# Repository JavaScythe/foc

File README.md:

# foc
Hyper realistic two-channel sim racing seatbelt tensioner with two 48V 54+54A FOC motors and controller that blows commercial 1300$ solutions out of the water

Specifically, it is high torque low latency that comes with its own software with support for real dynamic frequency effects for haptic feedback

### PLEASE see [JOURNAL.md](JOURNAL.md)

### Why?
- HackClub's great initiative [highway](https://highway.hackclub.com): not just "free money" but a nice community of beginners and advanced that help each other
- Lack of respect for realism in sim racing: All too often "immersion" devices are just smoke and mirrors to generate profit, lacking careful design for realism, and the community defends this.
- Vastly overpriced consumer solutions: Really? 1300$ for something that can be surpassed by a consumer with 350$?
- Fun but complex to build toy: Using the rig is fun, but building stuff for it is better

### Pictures

### BOM
|Name          |Quantity|Price Total  |Link  |
|--------|-------|--------|------|
|ODrive3.6 56V|1|60$    |alibaba.com/product-detail/ODrive3-6-FOC-BLDC-Servo-Dual_1601406724288.html|
|S70BL146-430|2|120$|alibaba.com/product-detail/S70BL146-430-Brushless-Dc-Motor-High_1600943342358.html|
|4 Point Belt|1|19$|aliexpress.us/item/3256807037196658.html|
|2kw 40A 48V PSU|1|100$|alibaba.com/product-detail/High-Quality-2000W-48V-41-6A_1600901714728.html|
|SimHub License+Motion License|1|45€|simhubdash.com/simhub-motion-addon-licence/|

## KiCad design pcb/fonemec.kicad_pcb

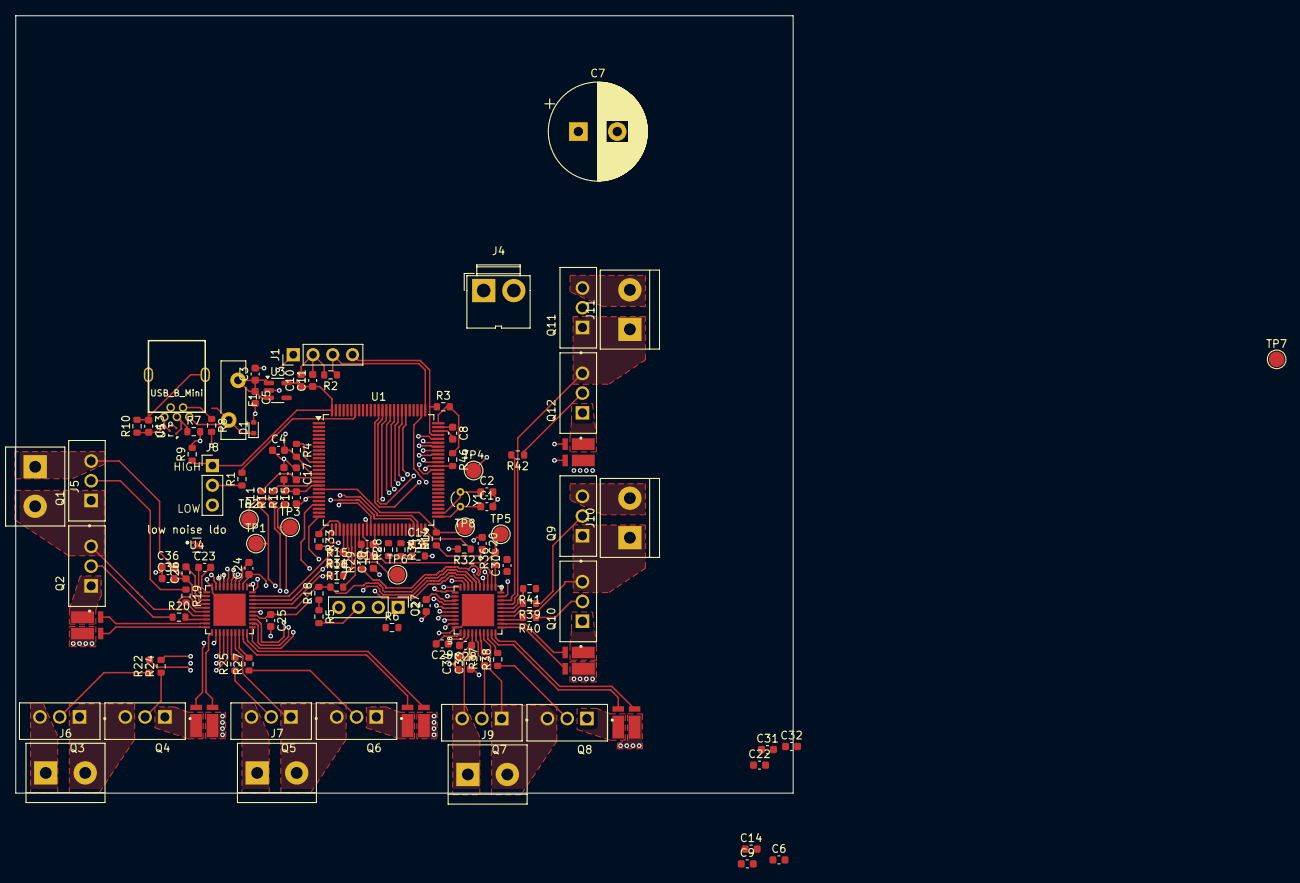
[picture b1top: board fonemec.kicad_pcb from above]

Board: 4 copper layers, 100.0 x 100.0 mm, 120 parts (0 on the bottom side), 122 nets.

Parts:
C1, C2: 22pF; C_0603_1608Metric
C3, C5, C8, C12: 10 µF X7R; C_0603_1608Metric
C4: 0.1uF; C_0603_1608Metric
C6, C10: 10 0nF; C_0603_1608Metric
C7: Low-ESR polymer electrolytic 470uF 63V; CP_Radial_D12.5mm_P5.00mm
C9, C11: 1 µF; C_0603_1608Metric
C13: 1 nF; C_0603_1608Metric
C14, C22, C33, C36: 22uf Ceramic MLCC X7R; C_0603_1608Metric
C15, C16, C17, C18, C19, C20: 1nF; C_0603_1608Metric
C23, C29: X7R 47nF >48V; C_0603_1608Metric
C24, C27: X7R 1uF 6.3V; C_0603_1608Metric
C25, C30: X7R 0.1uF 6.3V; C_0603_1608Metric
C26, C28: X7R 1uF 16V; C_0603_1608Metric
C31: X7R 22uF >63V; C_0603_1608Metric
C32: X7R 0.1uF >63V; C_0603_1608Metric
C34, C35: 0.1uf Ceramic MLCC X7R; C_0603_1608Metric
D1: PESD5V0S1BA; D_SOD-523
F1: ASMD050-2; Fuse_Bourns_MF-RG400
J1: 01x04 SWD; PinHeader_1x04_P2.54mm_Vertical
J2: 01x04 USART; PinHeader_1x04_P2.54mm_Vertical
J3: USB_B_Mini; USB-Mini-B_2leg
J4: 01x02 48V; JWT_A3963_1x02_P3.96mm_Vertical
J5: Motor 1 Phase A; TerminalBlock_bornier-2_P5.08mm
J6: Motor 1 Phase B; TerminalBlock_bornier-2_P5.08mm
J7: Motor 1 Phase C; TerminalBlock_bornier-2_P5.08mm
J8: Conn_01x03_Pin; PinHeader_1x03_P2.54mm_Vertical
J9: Motor 2 Phase A; TerminalBlock_bornier-2_P5.08mm
J10: Motor 2 Phase B; TerminalBlock_bornier-2_P5.08mm
J11: Motor 2 Phase C; TerminalBlock_bornier-2_P5.08mm
Q1, Q2, Q3, Q4, Q5, Q6, Q7, Q8, Q9, Q10, Q11, Q12: CSD19536KCS; TO254P1036X470X1965-3
R1, R2, R3, R4, R5: 100K; R_0603_1608Metric
R6: 1K; R_0603_1608Metric
R7, R8, R15, R16, R17, R28, R31, R35: 22; R_0603_1608Metric
R9: 1.5K; R_0603_1608Metric
R10: 1M; R_0603_1608Metric
R11, R12, R13, R14, R29, R36: 100; R_0603_1608Metric
R18, R32, R33, R34, R46: 10K; R_0603_1608Metric
R19, R20, R22, R24, R25, R27, R37, R38, R39, R40, R41, R42: 2; R_0603_1608Metric
R21, R23, R26, R43, R44, R45: R_Shunt; RES_WSK12161L000FEA
TP1: TP1SOA; TestPoint_Pad_D2.0mm
TP2: TP1SOB; TestPoint_Pad_D2.0mm
TP3: TP1SOC; TestPoint_Pad_D2.0mm
TP4, TP7: TPGND; TestPoint_Pad_D2.0mm
TP5: TP2SOC; TestPoint_Pad_D2.0mm
TP6: TP2SOB; TestPoint_Pad_D2.0mm
TP8: TP2SOA; TestPoint_Pad_D2.0mm
U1: STM32F405VGTx; LQFP-100_14x14mm_P0.5mm
U3: AP2112K-3.3; SOT-23-5
U4: PTPS7A0218PDQNR; DQN0004A-MFG
U5: TPD2EUSB30; Texas_DRT-3
U7, U8: DRV8323SRTAT; QFN50P600X600X80-41N415X415
Y1: 8Mhz; Crystal_DS26_D2.0mm_L6.0mm_Vertical

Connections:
1CAL: U1.65 (PC8), U7.31 (CAL)
1ENABLE: U1.63 (PC6), U7.30 (ENABLE)
1GHA: R19.2, U7.6 (GHA)
1GHB: R22.2, U7.15 (GHB)
1GHC: R25.2, U7.16 (GHC)
1GLA: R20.2, U7.8 (GLA)
1GLB: R24.2, U7.13 (GLB)
1GLC: R27.2, U7.18 (GLC)
1INHA: U1.67 (PA8), U7.34 (INHA)
1INHB: U1.69 (PA10), U7.36 (INHB)
1INHC: U1.48 (PB11), U7.38 (INHC)
1INLA: U1.68 (PA9), U7.35 (INLA)
1INLB: U1.36 (PB1), U7.37 (INLB)
1INLC: U1.47 (PB10), U7.39 (INLC)
1NFAULT: R46.2, U1.64 (PC7), U7.25 (NFAULT)
1SAN: R21.2, U7.10 (SNA)
1SAP: R21.3, U7.9 (SPA)
1SBN: R23.2, U7.11 (SNB)
1SBP: R23.3, U7.12 (SPB)
1SCN: R26.2, U7.20 (SNC)
1SCP: R26.3, U7.19 (SPC)
1SHA: J5.2, Q1.1 (S), Q2.5 (D), U7.5 (VDRAIN), U7.7 (SHA)
1SHB: J6.2, Q3.1 (S), Q4.5 (D), U7.14 (SHB)
1SHC: J7.2, Q5.1 (S), Q6.5 (D), U7.17 (SHC)
1SOA: C17.2, R11.2, U1.15 (PC0)
1SOB: C16.2, R12.2, U1.16 (PC1)
1SOC: C15.2, R13.2, U1.17 (PC2)
2CAL: U1.88 (PD7), U8.31 (CAL)
2ENABLE: U1.87 (PD6), U8.30 (ENABLE)
2GHA: R37.2, U8.6 (GHA)
2GHB: R39.2, U8.15 (GHB)
2GHC: R41.2, U8.16 (GHC)
2GLA: R38.2, U8.8 (GLA)
2GLB: R40.2, U8.13 (GLB)
2GLC: R42.2, U8.18 (GLC)
2INHA: U1.81 (PD0), U8.34 (INHA)
2INHB: U1.83 (PD2), U8.36 (INHB)
2INHC: U1.85 (PD4), U8.38 (INHC)
2INLA: U1.82 (PD1), U8.35 (INLA)
2INLB: U1.84 (PD3), U8.37 (INLB)
2INLC: U1.86 (PD5), U8.39 (INLC)
2NFAULT: R32.2, U1.77 (PA15), U8.25 (NFAULT)
2SAN: R43.2, U8.10 (SNA)
2SAP: R43.3, U8.9 (SPA)
2SBN: R44.2, U8.11 (SNB)
2SBP: R44.3, U8.12 (SPB)
2SCN: R45.2, U8.20 (SNC)
2SCP: R45.3, U8.19 (SPC)
2SHA: J9.2, Q7.1 (S), Q8.5 (D), U8.5 (VDRAIN), U8.7 (SHA)
2SHB: J10.1, Q9.1 (S), Q10.5 (D), U8.14 (SHB)
2SHC: J11.1, Q11.1 (S), Q12.5 (D), U8.17 (SHC)
2SOA: R14.2, TP8.1, U1.18 (PC3)
2SOB: C19.2, R29.2, TP6.1, U1.33 (PC4)
2SOC: C18.2, R36.2, TP5.1, U1.34 (PC5)
+5V: C3.1, C5.1, F1.1, U3.1 (VIN), U3.3 (EN), U4.3 (EN), U4.4 (IN)
AGND: C24.1, C25.2, C27.1, C30.2, U7.32 (AGND), U8.32 (AGND)
GND: C1.2, C2.2, C3.2, C4.1, C5.2, C6.2, C7.1, C8.1, C9.2, C10.2, C11.2, C12.1, C13.2, C14.1, C15.1, C16.1, C17.1, C18.1, C19.1, C20.1, C22.1, C31.1, C32.1, C33.1, C34.1, C35.1, C36.1, D1.2 (A), J1.2, J2.2, J3.5 (GND), J4.1, J8.3, R2.2, R10.1, R21.1, R23.1, R26.1, R43.1, R44.1, R45.1, TP4.1, TP7.1, U1.10 (VSS), U1.20 (VSSA), U1.27 (VSS), U1.37 (PB2), U1.74 (VSS), U1.99 (VSS), U3.2 (GND), U4.2 (GND), U5.3 (GND), U7.40 (PGND), U7.41 (EXP), U8.40 (PGND), U8.41 (EXP)
NRST: C4.2, J1.1, R4.2, U1.14 (NRST)
unnamed: C31.2, C32.2
unnamed: D1.1 (K), F1.2, J3.1 (VBUS)
unnamed: J1.3, R2.1, U1.76 (PA14)
unnamed: J1.4, R3.1, U1.72 (PA13)
unnamed: J2.1, R6.2
unnamed: J3.3 (D+), R7.1, U5.1 (D+)
unnamed: J3.2 (D-), R8.1, U5.2 (D-)
unnamed: C13.1, J3.6 (Shield), R10.2
unnamed: J8.2, R1.1
unnamed: Q1.4 (G), R19.1
unnamed: Q2.4 (G), R20.1
unnamed: Q2.1 (S), R21.4
unnamed: Q3.4 (G), R22.1
unnamed: Q4.4 (G), R24.1
unnamed: Q4.1 (S), R23.4
unnamed: Q5.4 (G), R25.1
unnamed: Q6.4 (G), R27.1
unnamed: Q6.1 (S), R26.4
unnamed: Q7.4 (G), R37.1
unnamed: Q8.4 (G), R38.1
unnamed: Q8.1 (S), R43.4
unnamed: Q9.4 (G), R39.1
unnamed: Q10.4 (G), R40.1
unnamed: Q10.1 (S), R44.4
unnamed: Q11.4 (G), R41.1
unnamed: Q12.4 (G), R42.1
unnamed: Q12.1 (S), R45.4
unnamed: R1.2, U1.94 (BOOT0)
unnamed: R15.2, U1.30 (PA5)
unnamed: R16.2, U1.31 (PA6)
unnamed: R17.2, U1.32 (PA7)
unnamed: R28.2, U1.35 (PB0)
unnamed: C1.1, U1.51 (PB12), Y1.2
unnamed: C2.1, U1.52 (PB13), Y1.1
unnamed: C12.2, U1.49 (VCAP_1)
unnamed: C8.2, U1.73 (VCAP_2)
unnamed: C23.1, U7.2 (CPH)
unnamed: C23.2, U7.1 (CPL)
unnamed: C24.2, U7.33 (DVDD)
unnamed: R31.2, U7.29 (NSCS)
unnamed: R11.1, TP1.1, U7.23 (SOA)
unnamed: R12.1, TP2.1, U7.22 (SOB)
unnamed: R13.1, TP3.1, U7.21 (SOC)
unnamed: C26.2, U7.3 (VCP)
unnamed: C29.1, U8.2 (CPH)
unnamed: C29.2, U8.1 (CPL)
unnamed: C27.2, U8.33 (DVDD)
unnamed: R35.2, U8.29 (NSCS)
unnamed: C20.2, R14.1, U8.23 (SOA)
unnamed: R29.1, U8.22 (SOB)
unnamed: R36.1, U8.21 (SOC)
unnamed: C28.2, U8.3 (VCP)
SPI_MISO: R16.1, U7.27 (SDI), U8.27 (SDI)
SPI_MOSI: R17.1, R18.2, U7.26 (SDO), U8.26 (SDO)
SPI_NSCS_1: R31.1, R33.2, U1.29 (PA4)
SPI_NSCS_2: R28.1, R34.2, R35.1
SPI_SCK: R15.1, U7.28 (SCLK), U8.28 (SCLK)
USB D+: R7.2, R9.2, U1.71 (PA12)
USB D-: R8.2, U1.70 (PA11)
USRX: J2.3, R5.2, U1.26 (PA3)
USTX: J2.4, U1.25 (PA2)
VDD: C10.1, C11.1, J8.1, R3.2, R4.1, R5.1, R6.1, R9.1, R18.1, R32.1, R33.1, R34.1, R46.1, U1.11 (VDD), U1.19 (VDD), U1.28 (VDD), U1.50 (VDD), U1.75 (VDD), U1.100 (VDD), U3.5 (VOUT)
VDDA: C6.1, C9.1, C25.1, C30.1, U1.22 (VDDA), U4.1 (OUT), U7.24 (VREF), U8.24 (VREF)
VM: C7.2, C14.2, C22.2, C26.1, C28.1, C33.2, C34.2, C35.2, C36.2, J4.2, J5.1, J6.1, J7.1, J9.1, J10.2, J11.2, Q1.5 (D), Q3.5 (D), Q5.5 (D), Q7.5 (D), Q9.5 (D), Q11.5 (D), U7.4 (VM), U8.4 (VM)

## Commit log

2025-06-06 set CDC native 0x0 mode
2025-06-06 Upload FEM included CAD files
2025-06-07 Create root
